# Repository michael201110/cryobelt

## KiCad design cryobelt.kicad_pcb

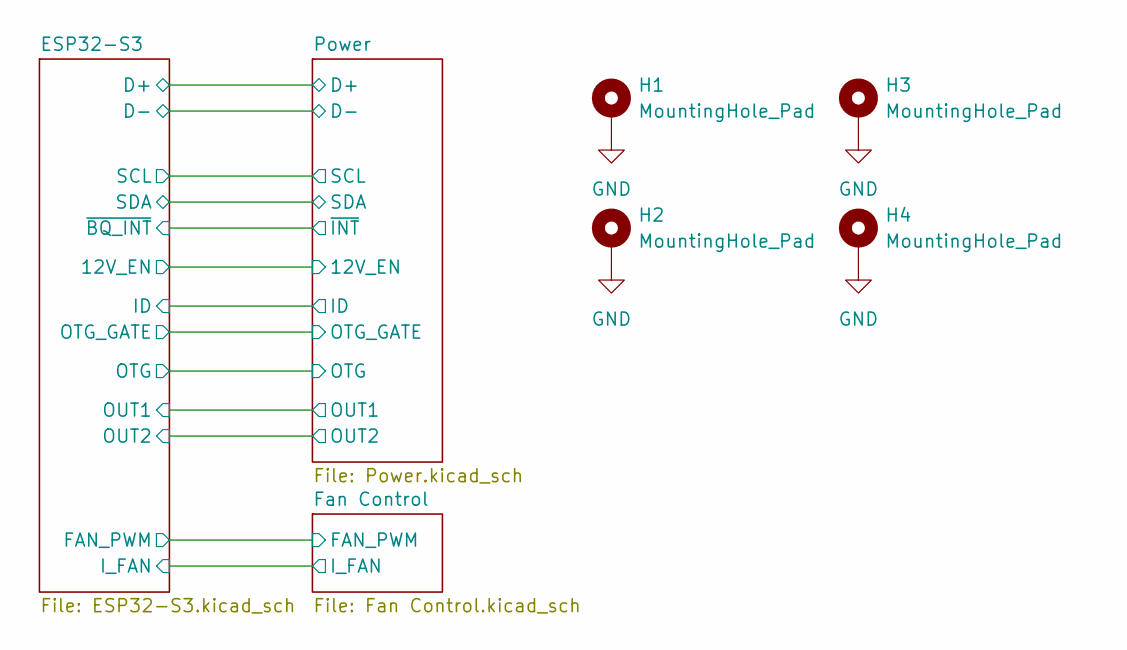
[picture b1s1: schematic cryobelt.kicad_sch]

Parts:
H1, H2, H3, H4: MountingHole_Pad; MountingHole_2.2mm_M2_Pad_TopBottom

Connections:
GND: H1.1 (1_1), H2.1 (1_1), H3.1 (1_1), H4.1 (1_1); also elsewhere on the board

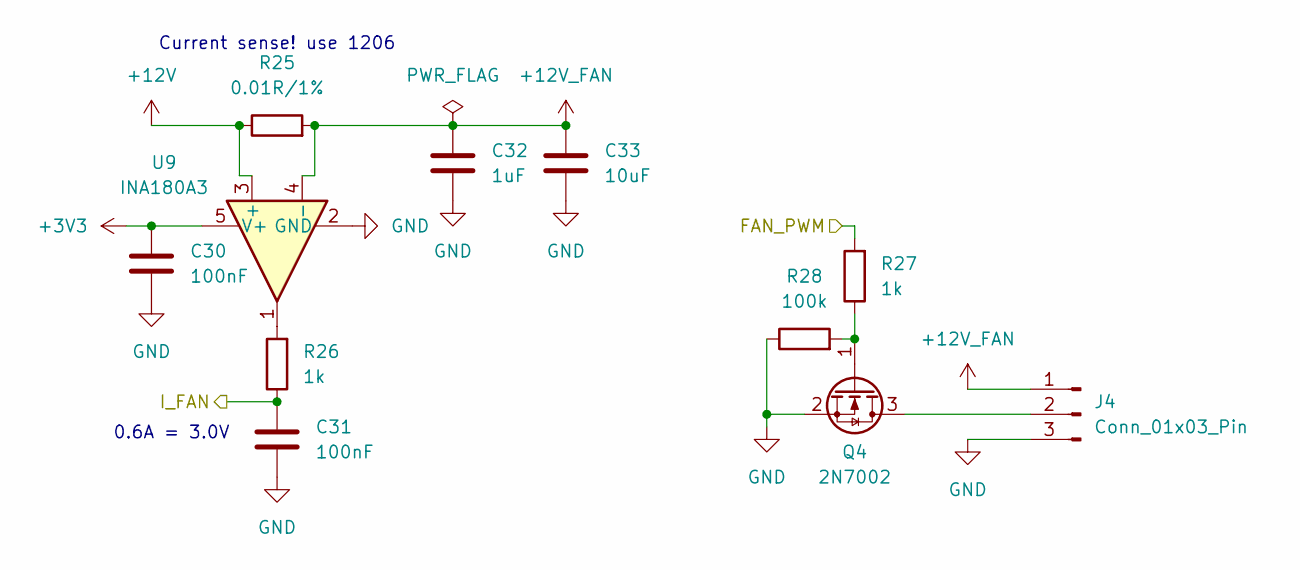
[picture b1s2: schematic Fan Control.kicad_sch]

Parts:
C30, C31: 100nF; C_0603_1608Metric; MPN CC0603KRX7R9BB104; LCSC Part # C14663
C32: 1uF; C_0603_1608Metric; MPN CL10A105KB8NNNC; LCSC Part # C15849
C33: 10uF; C_0603_1608Metric; MPN CL10A106MA8NRNC; LCSC Part # C96446
J4: Conn_01x03_Pin; JST_GH_SM03B-GHS-TB_1x03-1MP_P1.25mm_Horizontal; MPN SM03B-GHS-TB(LF)(SN); LCSC Part # C514175
Q4: 2N7002; SOT-23; MPN 2N7002; LCSC Part # C8545
R25: 0.01R/1%; R_1206_3216Metric; MPN FRM121WFR010TM; LCSC Part # C7467248
R26, R27: 1k; R_0603_1608Metric; MPN 0603WAF1001T5E; LCSC Part # C21190
R28: 100k; R_0603_1608Metric; MPN 0603WAF1003T5E; LCSC Part # C25803
U9: INA180A3; SOT-23-5; MPN INA180A3IDBVR; LCSC Part # C122882

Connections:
+3V3: C30.1, U9.5 (V+); also elsewhere on the board
+12V: R25.1, U9.3 (+); also elsewhere on the board
+12V_FAN: C32.1, C33.1, J4.1, R25.2, U9.4 (-)
/ESP32-S3/FAN_PWM: R27.2; also elsewhere on the board
/ESP32-S3/I_FAN: C31.1, R26.1; also elsewhere on the board
GND: C30.2, C31.2, C32.2, C33.2, J4.3, Q4.2 (S), R28.1, U9.2 (GND); also elsewhere on the board
unnamed: J4.2, Q4.3 (D)
unnamed: Q4.1 (G), R27.1, R28.2
unnamed: R26.2, U9.1

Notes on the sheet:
0.6A = 3.0V
Current sense! use 1206

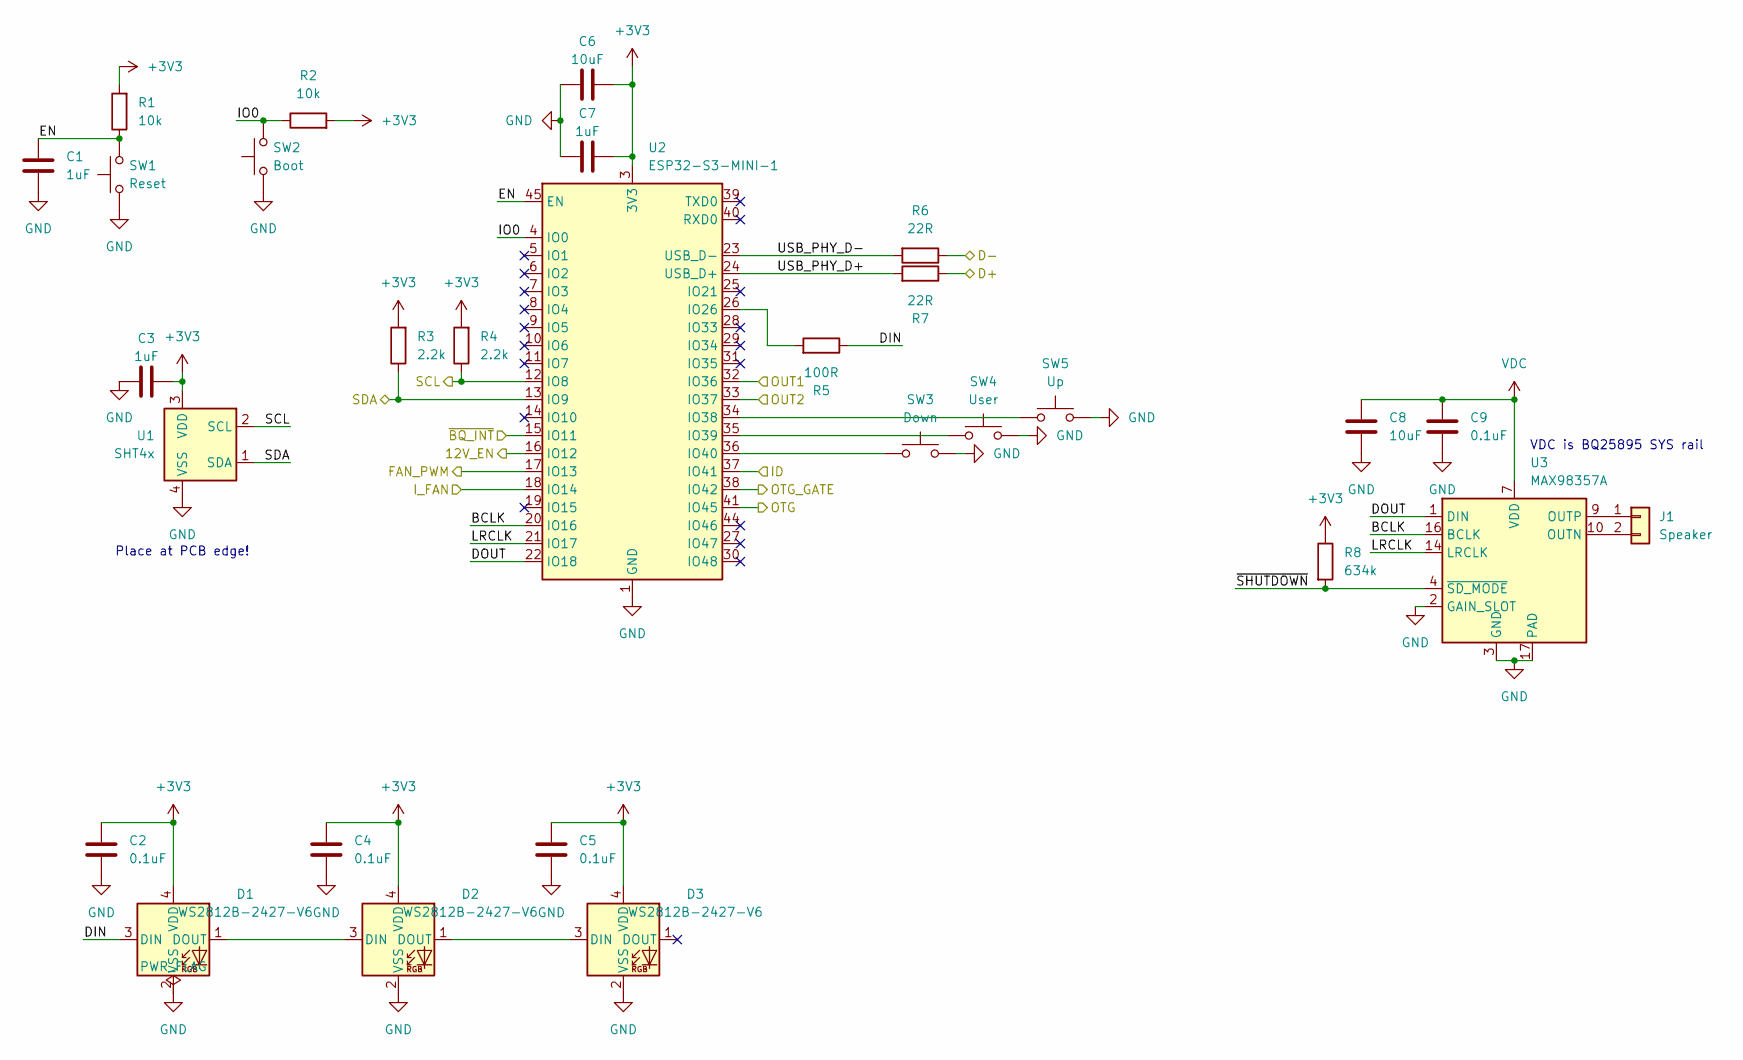
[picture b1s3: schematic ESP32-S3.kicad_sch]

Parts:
C1, C3, C7: 1uF; C_0603_1608Metric; MPN CL10A105KB8NNNC; LCSC Part # C15849
C2, C4, C5: 0.1uF; C_0402_1005Metric; MPN CL05B104KO5NNNC; LCSC Part # C1525
C6, C8: 10uF; C_0603_1608Metric; MPN CL10A106KP8NNNC; LCSC Part # C19702
C9: 0.1uF; C_0603_1608Metric; MPN CC0603KRX7R9BB104; LCSC Part # C14663
D1, D2, D3: WS2812B-2427-V6; WS2812B-2427-V6_Rotated180; MPN WS2812B-2427-V6; LCSC Part # C52941389
J1: Speaker; SolderWire-0.1sqmm_1x02_P3.6mm_D0.4mm_OD1mm
R1, R2: 10k; R_0603_1608Metric; MPN 0603WAF1002T5E; LCSC Part # C25804
R3, R4: 2.2k; R_0603_1608Metric; MPN 0603WAF2201T5E; LCSC Part # C4190
R5: 100R; R_0603_1608Metric; MPN 0603WAF1000T5E; LCSC Part # C22775
R6, R7: 22R; R_0603_1608Metric; MPN 0603WAF220JT5E; LCSC Part # C23345
R8: 634k; R_0603_1608Metric; MPN RC0603FR-07634KL; LCSC Part # C273753
SW1: Reset; SW_Push_1P1T_XKB_TS-1187A; MPN TS-1187A-B-A-B; LCSC Part # C318884
SW2: Boot; SW_Push_1P1T_XKB_TS-1187A; MPN TS-1187A-B-A-B; LCSC Part # C318884
SW3: Down; PG1316S
SW4: User; PG1316S
SW5: Up; PG1316S
U1: SHT4x; Sensirion_DFN-4_1.5x1.5mm_P0.8mm_SHT4x_NoCentralPad; MPN SHT40-AD1B-R2; LCSC Part # C2909890
U2: ESP32-S3-MINI-1; MPN ESP32-S3-MINI-1-N8; LCSC Part # C2913206
U3: MAX98357A; TQFN-16-1EP_3x3mm_P0.5mm_EP1.23x1.23mm; MPN MAX98357AETE+T; LCSC Part # C910544

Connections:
+3V3: C2.1, C3.2, C4.1, C5.1, C6.2, C7.2, D1.4 (VDD), D2.4 (VDD), D3.4 (VDD), R1.2, R2.2, R3.2, R4.2, R8.1, U1.3 (VDD), U2.3 (3V3); also elsewhere on the board
/ESP32-S3/12V_EN: U2.16 (IO12); also elsewhere on the board
/ESP32-S3/BCLK: U2.20 (IO16), U3.16 (BCLK)
/ESP32-S3/D+: R7.1; also elsewhere on the board
/ESP32-S3/D-: R6.1; also elsewhere on the board
/ESP32-S3/DIN: D1.3 (DIN), R5.1
/ESP32-S3/DOUT: U2.22 (IO18), U3.1 (DIN)
/ESP32-S3/EN: C1.1, R1.1, SW1.2, U2.45 (EN)
/ESP32-S3/FAN_PWM: U2.17 (IO13); also elsewhere on the board
/ESP32-S3/ID: U2.37 (IO41); also elsewhere on the board
/ESP32-S3/IO0: R2.1, SW2.2, U2.4 (IO0)
/ESP32-S3/I_FAN: U2.18 (IO14); also elsewhere on the board
/ESP32-S3/LRCLK: U2.21 (IO17), U3.14 (LRCLK)
/ESP32-S3/OTG: U2.41 (IO45); also elsewhere on the board
/ESP32-S3/OTG_GATE: U2.38 (IO42); also elsewhere on the board
/ESP32-S3/OUT1: U2.32 (IO36); also elsewhere on the board
/ESP32-S3/OUT2: U2.33 (IO37); also elsewhere on the board
/ESP32-S3/SCL: R4.1, U1.2 (SCL), U2.12 (IO8); also elsewhere on the board
/ESP32-S3/SDA: R3.1, U1.1 (SDA), U2.13 (IO9); also elsewhere on the board
/ESP32-S3/USB_PHY_D+: R7.2, U2.24 (USB_D+)
/ESP32-S3/USB_PHY_D-: R6.2, U2.23 (USB_D-)
/ESP32-S3/~BQ_INT: U2.15 (IO11); also elsewhere on the board
/ESP32-S3/~SHUTDOWN: R8.2, U3.4 (~SD_MODE)
GND: C1.2, C2.2, C3.1, C4.2, C5.2, C6.1, C7.1, C8.2, C9.2, D1.2 (VSS), D2.2 (VSS), D3.2 (VSS), SW1.1, SW2.1, SW3.2, SW4.2, SW5.2, U1.4 (VSS), U2.1 (GND), U2.2 (GND), U2.42 (GND), U2.43 (GND), U2.46 (GND), U2.47 (GND), U2.48 (GND), U2.49 (GND), U2.50 (GND), U2.51 (GND), U2.52 (GND), U2.53 (GND), U2.54 (GND), U2.55 (GND), U2.56 (GND), U2.57 (GND), U2.58 (GND), U2.59 (GND), U2.60 (GND), U2.61 (GND), U2.62 (GND), U2.63 (GND), U2.64 (GND), U2.65 (GND), U3.2 (GAIN_SLOT), U3.3 (GND), U3.11 (GND), U3.15 (GND), U3.17 (PAD); also elsewhere on the board
unnamed: D1.1 (DOUT), D2.3 (DIN)
unnamed: D2.1 (DOUT), D3.3 (DIN)
unnamed: J1.1, U3.9 (OUTP)
unnamed: J1.2, U3.10 (OUTN)
unnamed: R5.2, U2.26 (IO26)
unnamed: SW5.1, U2.34 (IO38)
unnamed: SW4.1, U2.35 (IO39)
unnamed: SW3.1, U2.36 (IO40)
VDC: C8.1, C9.1, U3.7 (VDD), U3.8 (VDD); also elsewhere on the board

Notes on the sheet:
VDC is BQ25895 SYS rail
Place at PCB edge!

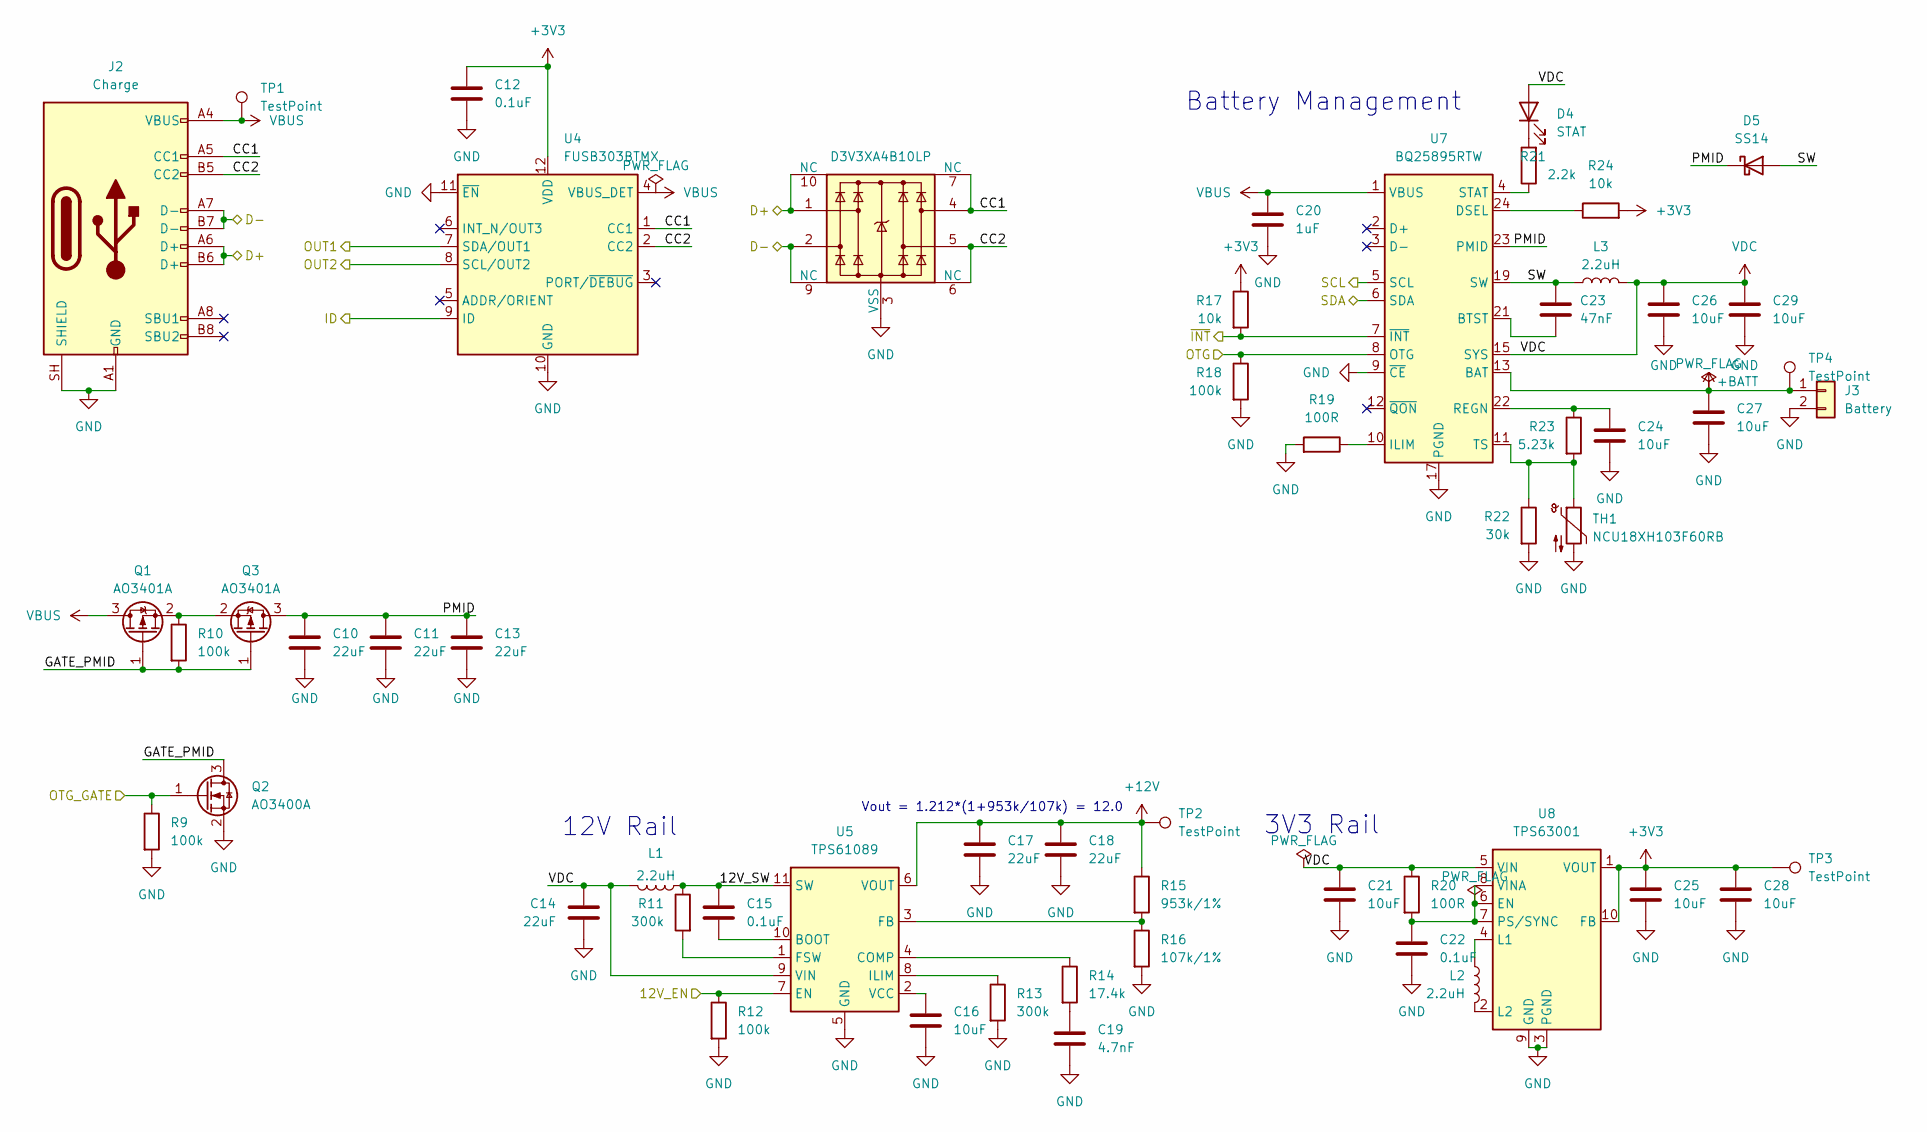
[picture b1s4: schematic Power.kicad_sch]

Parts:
C10, C11, C13, C17, C18: 22uF; C_0805_2012Metric; MPN CL21A226MAQNNNE; LCSC Part # C45783
C12, C15, C22: 0.1uF; C_0603_1608Metric; MPN CC0603KRX7R9BB104; LCSC Part # C14663
C14: 22uF; C_0603_1608Metric; MPN CL10A226MQ8NRNC; LCSC Part # C59461
C16, C21, C24, C25, C26, C27, C28, C29: 10uF; C_0603_1608Metric; MPN CL10A106KP8NNNC; LCSC Part # C19702
C19: 4.7nF; C_0603_1608Metric; MPN 0603B472K500NT; LCSC Part # C53987
C20: 1uF; C_0603_1608Metric; MPN CL10A105KB8NNNC; LCSC Part # C15849
C23: 47nF; C_0603_1608Metric; MPN CL10B473KB8NNNC; LCSC Part # C1622
D4: STAT; LED_0603_1608Metric; MPN KT-0603R; LCSC Part # C2286
D5: SS14; D_SMA; MPN SS14; LCSC Part # C2480
J2: Charge; USB_C_Receptacle_GCT_USB4110; MPN USB4110-GF-A; LCSC Part # C5143397
J3: Battery; JST_PH_S2B-PH-K_1x02_P2.00mm_Horizontal; MPN S2B-PH-K-S(LF)(SN); LCSC Part # C173752
L1, L2, L3: 2.2uH; L_Changjiang_FNR4030S; MPN FEXU0420S2R2MBS; LCSC Part # C54777963
Q1, Q3: AO3401A; SOT-23; MPN AO3401A; LCSC Part # C15127
Q2: AO3400A; SOT-23; MPN AO3400A; LCSC Part # C20917
R9, R10, R12, R18: 100k; R_0603_1608Metric; MPN 0603WAF1003T5E; LCSC Part # C25803
R11, R13: 300k; R_0603_1608Metric; MPN 0603WAF3003T5E; LCSC Part # C23024
R14: 17.4k; R_0603_1608Metric; MPN RC0603FR-0717K4L; LCSC Part # C185365
R15: 953k/1%; R_0603_1608Metric; MPN ERJ3EKF9533V; LCSC Part # C403405
R16: 107k/1%; R_0603_1608Metric; MPN RC0603FR-07107KL; LCSC Part # C245894
R17, R24: 10k; R_0603_1608Metric; MPN 0603WAF1002T5E; LCSC Part # C25804
R19, R20: 100R; R_0603_1608Metric; MPN 0603WAF1000T5E; LCSC Part # C22775
R21: 2.2k; R_0603_1608Metric; MPN 0603WAF2201T5E; LCSC Part # C4190
R22: 30k; R_0603_1608Metric; MPN 0603WAF3002T5E; LCSC Part # C22984
R23: 5.23k; R_0603_1608Metric; MPN RC0603FR-075K23L; LCSC Part # C185317
TH1: NCU18XH103F60RB; R_0603_1608Metric; MPN NCU18XH103F60RB; LCSC Part # C440252
TP1, TP2, TP3, TP4: TestPoint; TestPoint_Pad_D2.0mm
U4: FUSB303BTMX; Texas_X2QFN-12_1.6x1.6mm_P0.4mm; MPN FUSB303BTMX; LCSC Part # C895444
U5: TPS61089; Texas_VQFN-RNR0011A-11; MPN TPS61089RNRR; LCSC Part # C165129
U6: D3V3XA4B10LP; Diodes_UDFN-10_1x2.5mm_P0.5mm; MPN D3V3XA4B10LP-7; LCSC Part # C1980462
U7: BQ25895RTW; Texas_RTW_WQFN-24-1EP_4x4mm_P0.5mm_EP2.7x2.7mm_ThermalVias; MPN BQ25895RTWR; LCSC Part # C80200
U8: TPS63001; Texas_DRC0010J_ThermalVias; MPN TPS63001DRCR; LCSC Part # C28060

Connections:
+3V3: C12.1, C25.1, C28.1, R17.1, R24.2, TP3.1 (1_1), U4.12 (VDD), U8.1 (VOUT), U8.10 (FB); also elsewhere on the board
+12V: C17.1, C18.1, R15.1, TP2.1 (1_1), U5.6 (VOUT); also elsewhere on the board
+BATT: C27.1, J3.1, TP4.1 (1_1), U7.13 (BAT), U7.14 (BAT)
/ESP32-S3/12V_EN: R12.1, U5.7 (EN); also elsewhere on the board
/ESP32-S3/D+: J2.A6 (D+), J2.B6 (D+), U6.1, U6.10 (NC); also elsewhere on the board
/ESP32-S3/D-: J2.A7 (D-), J2.B7 (D-), U6.2, U6.9 (NC); also elsewhere on the board
/ESP32-S3/ID: U4.9 (ID); also elsewhere on the board
/ESP32-S3/OTG: R18.1, U7.8 (OTG); also elsewhere on the board
/ESP32-S3/OTG_GATE: Q2.1 (G), R9.1; also elsewhere on the board
/ESP32-S3/OUT1: U4.7 (SDA/OUT1); also elsewhere on the board
/ESP32-S3/OUT2: U4.8 (SCL/OUT2); also elsewhere on the board
/ESP32-S3/SCL: U7.5 (SCL); also elsewhere on the board
/ESP32-S3/SDA: U7.6 (SDA); also elsewhere on the board
/ESP32-S3/~BQ_INT: R17.2, U7.7 (~INT); also elsewhere on the board
/Power/12V_SW: C15.1, L1.2, R11.1, U5.11 (SW)
/Power/CC1: J2.A5 (CC1), U4.1 (CC1), U6.4, U6.7 (NC)
/Power/CC2: J2.B5 (CC2), U4.2 (CC2), U6.5, U6.6 (NC)
/Power/GATE_PMID: Q1.1 (G), Q2.3 (D), Q3.1 (G), R10.2
/Power/PMID: C10.1, C11.1, C13.1, D5.1 (K), Q3.3 (D), U7.23 (PMID)
/Power/SW: C23.1, D5.2 (A), L3.1, U7.19 (SW), U7.20 (SW)
GND: C10.2, C11.2, C12.2, C13.2, C14.2, C16.2, C17.2, C18.2, C19.2, C20.2, C21.2, C22.2, C24.2, C25.2, C26.2, C27.2, C28.2, C29.2, J2.A1 (GND), J2.A12 (GND), J2.B1 (GND), J2.B12 (GND), J2.SH (SHIELD), J3.2, Q2.2 (S), R9.2, R12.2, R13.2, R16.2, R18.2, R19.2, R22.2, TH1.2, U4.10 (GND), U4.11 (~EN), U5.5 (GND), U6.3 (VSS), U6.8 (VSS), U7.9 (~CE), U7.17 (PGND), U7.18 (PGND), U7.25 (PGND), U8.3 (PGND), U8.9 (GND), U8.11 (PGND); also elsewhere on the board
unnamed: C19.1, R14.2
unnamed: D4.1 (K), R21.2
unnamed: Q1.2 (S), Q3.2 (S), R10.1
unnamed: C15.2, U5.10 (BOOT)
unnamed: R14.1, U5.4 (COMP)
unnamed: R15.2, R16.1, U5.3 (FB)
unnamed: R11.2, U5.1 (FSW)
unnamed: R13.1, U5.8 (ILIM)
unnamed: C16.1, U5.2 (VCC)
unnamed: C23.2, U7.21 (BTST)
unnamed: R24.1, U7.24 (DSEL)
unnamed: R19.1, U7.10 (ILIM)
unnamed: C24.1, R23.1, U7.22 (REGN)
unnamed: R21.1, U7.4 (STAT)
unnamed: R22.1, R23.2, TH1.1, U7.11 (TS)
unnamed: C22.1, R20.2, U8.6 (EN), U8.7 (PS/SYNC), U8.8 (VINA)
unnamed: L2.2, U8.4 (L1)
unnamed: L2.1, U8.2 (L2)
VBUS: C20.1, J2.A4 (VBUS), J2.A9 (VBUS), J2.B4 (VBUS), J2.B9 (VBUS), Q1.3 (D), TP1.1 (1_1), U4.4 (VBUS_DET), U7.1 (VBUS)
VDC: C14.1, C21.1, C26.1, C29.1, D4.2 (A), L1.1, L3.2, R20.1, U5.9 (VIN), U7.15 (SYS), U7.16 (SYS), U8.5 (VIN); also elsewhere on the board

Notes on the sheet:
12V Rail
Battery Management
Vout = 1.212*(1+953k/107k) = 12.0
3V3 Rail

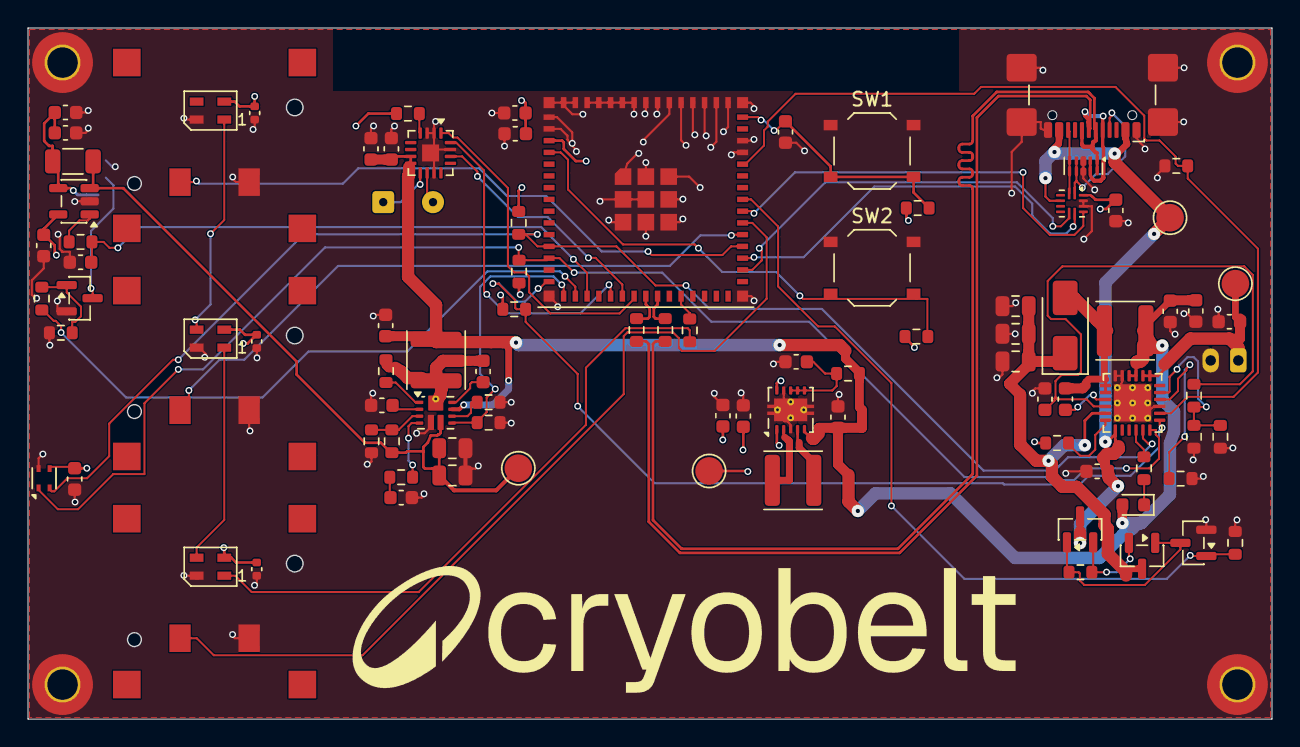
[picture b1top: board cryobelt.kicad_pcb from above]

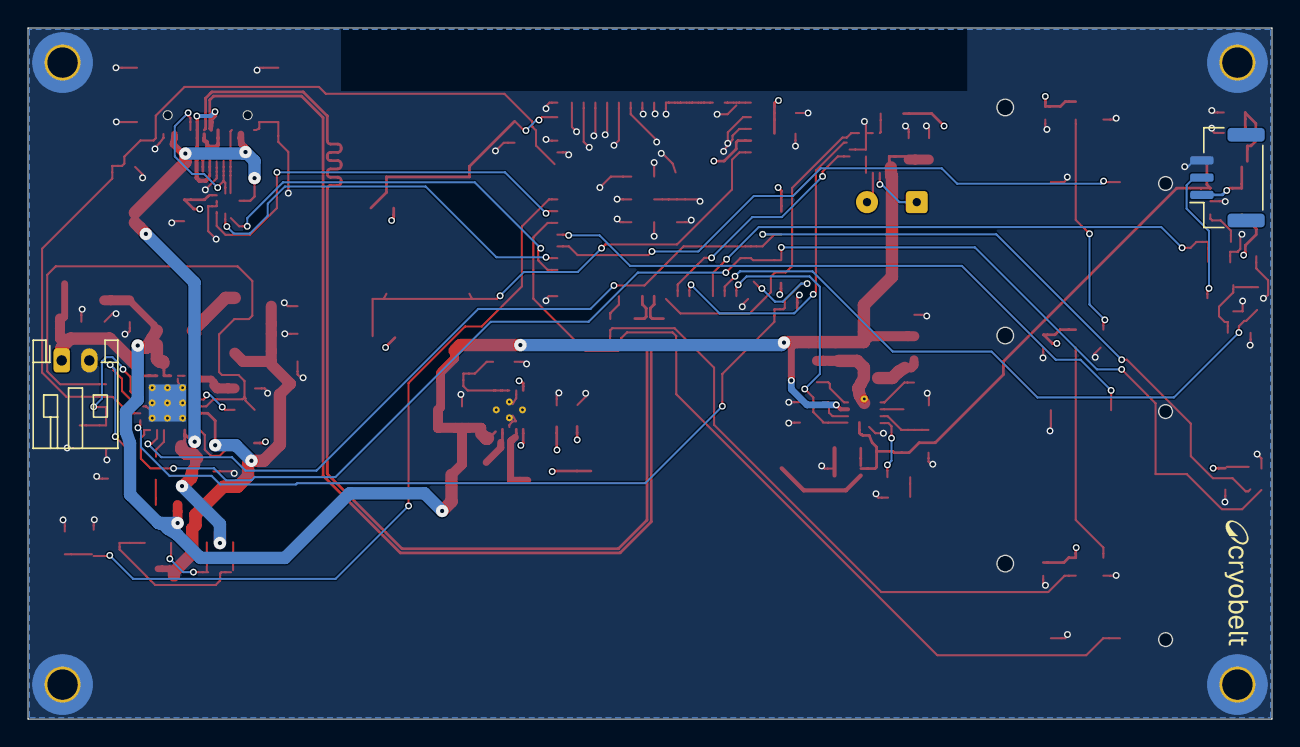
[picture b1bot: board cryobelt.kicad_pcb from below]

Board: 4 copper layers, 90.0 x 50.0 mm, 100 parts (2 on the bottom side), 64 nets.

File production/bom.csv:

Designator,Footprint,Quantity,Value,LCSC Part #
"C1, C20, C3, C32, C7",0603,5,1uF,C15849
"C10, C11, C13, C17, C18",0805,5,22uF,C45783
"C12, C15, C22, C9",0603,4,0.1uF,C14663
C14,0603,1,22uF,C59461
"C16, C21, C24, C25, C26, C27, C28, C29, C6, C8",0603,10,10uF,C19702
C19,0603,1,4.7nF,C53987
"C2, C4, C5",0402,3,0.1uF,C1525
C23,0603,1,47nF,C1622
"C30, C31",0603,2,100nF,C14663
C33,0603,1,10uF,C96446
"D1, D2, D3",WS2812B-2427-V6_Rotated180,3,WS2812B-2427-V6,C52941389
D4,0603,1,STAT,C2286
D5,D_SMA,1,SS14,C2480
J1,SolderWire-0.1sqmm_1x02_P3.6mm_D0.4mm_OD1mm,1,Speaker,
J2,USB_C_Receptacle_GCT_USB4110,1,Charge,C5143397
J3,JST_PH_S2B-PH-K_1x02_P2.00mm_Horizontal,1,Battery,C173752
J4,JST_GH_SM03B-GHS-TB_1x03-1MP_P1.25mm_Horizontal,1,Conn_01x03_Pin,C514175
"L1, L2, L3",L_Changjiang_FNR4030S,3,2.2uH,C54777963
"Q1, Q3",SOT-23,2,AO3401A,C15127
Q2,SOT-23,1,AO3400A,C20917
Q4,SOT-23,1,2N7002,C8545
"R1, R17, R2, R24",0603,4,10k,C25804
"R10, R12, R18, R28, R9",0603,5,100k,C25803
"R11, R13",0603,2,300k,C23024
R14,0603,1,17.4k,C185365
R15,0603,1,953k/1%,C403405
R16,0603,1,107k/1%,C245894
"R19, R20, R5",0603,3,100R,C22775
"R21, R3, R4",0603,3,2.2k,C4190
R22,0603,1,30k,C22984
R23,0603,1,5.23k,C185317
R25,1206,1,0.01R/1%,C7467248
"R26, R27",0603,2,1k,C21190
"R6, R7",0603,2,22R,C23345
R8,0603,1,634k,C273753
SW1,SW_Push_1P1T_XKB_TS-1187A,1,Reset,C318884
SW2,SW_Push_1P1T_XKB_TS-1187A,1,Boot,C318884
SW3,PG1316S,1,Down,
SW4,PG1316S,1,User,
SW5,PG1316S,1,Up,
TH1,0603,1,NCU18XH103F60RB,C440252
"TP1, TP2, TP3, TP4",TestPoint_Pad_D2.0mm,4,TestPoint,
U1,Sensirion_DFN-4_1.5x1.5mm_P0.8mm_SHT4x_NoCentralPad,1,SHT4x,C2909890
U2,ESP32-S3-MINI-1,1,ESP32-S3-MINI-1,C2913206
U3,TQFN-16-1EP_3x3mm_P0.5mm_EP1.23x1.23mm,1,MAX98357A,C910544
U4,Texas_X2QFN-12_1.6x1.6mm_P0.4mm,1,FUSB303BTMX,C895444
U5,Texas_VQFN-RNR0011A-11,1,TPS61089,C165129
U6,Diodes_UDFN-10_1x2.5mm_P0.5mm,1,D3V3XA4B10LP,C1980462
U7,Texas_RTW_WQFN-24-1EP_4x4mm_P0.5mm_EP2.7x2.7mm_ThermalVias,1,BQ25895RTW,C80200
U8,Texas_DRC0010J_ThermalVias,1,TPS63001,C28060
U9,SOT-23-5,1,INA180A3,C122882
